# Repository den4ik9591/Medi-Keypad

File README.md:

# MIDI Keypad

A custom MIDI keypad PCB with 7 capacitive touch keys, 3 mechanical buttons, a rotary encoder, 2 slide potentiometers and 3 RGB LEDs, all controlled by an ESP32-S3.

Made for Half Life (Week 3), following the MIDI keypad guide and then changing it to make it my own.

## What it has

- **7 touch keys:** large copper pads on the PCB that work like piano keys. I designed the key footprint myself.
- **3 Kailh Choc buttons:** for extra controls.
- **Rotary encoder (EC11):** for volume or scrolling.
- **2 slide potentiometers (Bourns PTA1543):** for smooth controls like pitch or volume.
- **3 SK6812 MINI-E LEDs:** chained on one data pin.
- **Microcontroller:** Waveshare ESP32-S3-Zero.
- **Board:** 2 layers, about 99.8 x 90.15 mm.

## Pin connections

| Part | ESP32-S3-Zero pin |
| --- | --- |
| Touch key 1 to 7 | GPIO 12, 10, 7, 11, 9, 8, 13 |
| Buttons SW1, SW2, SW3 | GPIO 4, 5, 6 |
| Slider RV2, RV1 | GPIO 1, 2 |
| LED data (DIN) | GPIO 3 |
| Encoder A, B | TX, RX |

Check these against the schematic before building, in case I changed a pin later.

## Files

- `Production/`: files for the PCB manufacturer
- `Images/`: screenshots of the design

## How I made it

1. Followed the guide and drew the schematic in KiCad. I changed the layout a few times so the PCB would be easier to wire.
2. Designed my own touch key footprint and tuned the dimensions.
3. Fixed the key connections in the schematic so every key reaches the ESP32.
4. Placed the parts and routed the board, using the Freerouting plugin for the rest.
5. Ran DRC and fixed the clearance and board edge errors.
6. Exported the production files with the JLCPCB Fabrication Toolkit and got a quote.

## Status

- [x] Schematic
- [x] PCB placed and routed
- [x] DRC fully clean
- [x] Case designed
- [x] Firmware
- [ ] Parts ordered and board built

## What I learned

- How to make a custom footprint for capacitive touch keys, and why touch pads should stay away from other copper.
- How nets work: a pad can only be wired to pads on the same net.
- How to use an autorouter and read a DRC report.

## Credits

Based on the MIDI Keypad guide: https://github.com/KaiPereira/MIDI-Keypad

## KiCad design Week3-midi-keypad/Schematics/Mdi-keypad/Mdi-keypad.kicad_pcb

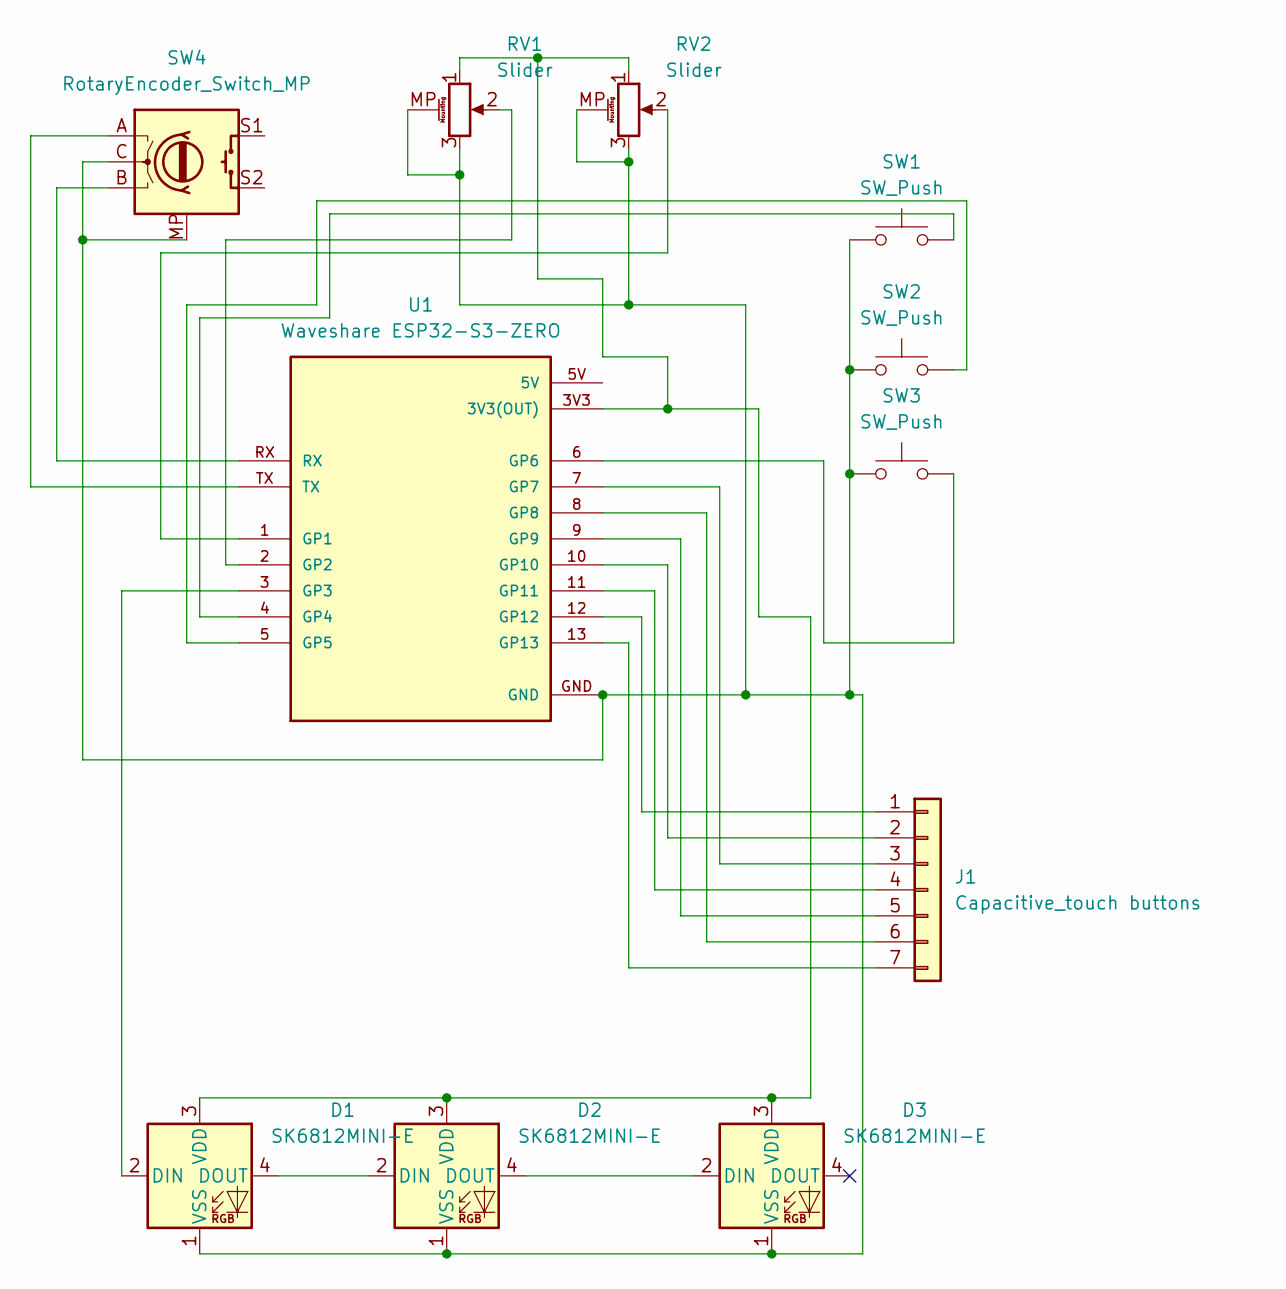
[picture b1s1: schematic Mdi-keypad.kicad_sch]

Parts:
D1, D2, D3: SK6812MINI-E; LED_SK6812MINI-E_3.2x2.8mm_P1.5mm_ReverseMount
J1: Capacitive_touch buttons; Untitled
RV1, RV2: Slider; Potentiometer_Bourns_PTA1543_Single_Slide
SW1, SW2, SW3: SW_Push; Kailh Choc Low-Profile Switches
SW4: RotaryEncoder_Switch_MP; RotaryEncoder_Alps_EC11E_Vertical_H20mm
U1: Waveshare ESP32-S3-ZERO; Waveshare ESP32-S3-Zero; PARTREV NA

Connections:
unnamed: D1.2 (DIN), U1.3 (GP3)
unnamed: D1.4 (DOUT), D2.2 (DIN)
unnamed: D1.3 (VDD), D2.3 (VDD), D3.3 (VDD), RV1.1, RV2.1, U1.3V3 (3V3(OUT))
unnamed: D1.1 (VSS), D2.1 (VSS), D3.1 (VSS), RV1.3, RV1.MP (MountPin), RV2.3, RV2.MP (MountPin), SW1.1, SW2.1, SW3.1, SW4.C, SW4.MP, U1.GND
unnamed: D2.4 (DOUT), D3.2 (DIN)
unnamed: J1.1, U1.12 (GP12)
unnamed: J1.2, U1.10 (GP10)
unnamed: J1.3, U1.7 (GP7)
unnamed: J1.4, U1.11 (GP11)
unnamed: J1.5, U1.9 (GP9)
unnamed: J1.6, U1.8 (GP8)
unnamed: J1.7, U1.13 (GP13)
unnamed: SW4.A, U1.TX
unnamed: SW4.B, U1.RX
unnamed: RV2.2, U1.1 (GP1)
unnamed: RV1.2, U1.2 (GP2)
unnamed: SW1.2, U1.4 (GP4)
unnamed: SW2.2, U1.5 (GP5)
unnamed: SW3.2, U1.6 (GP6)

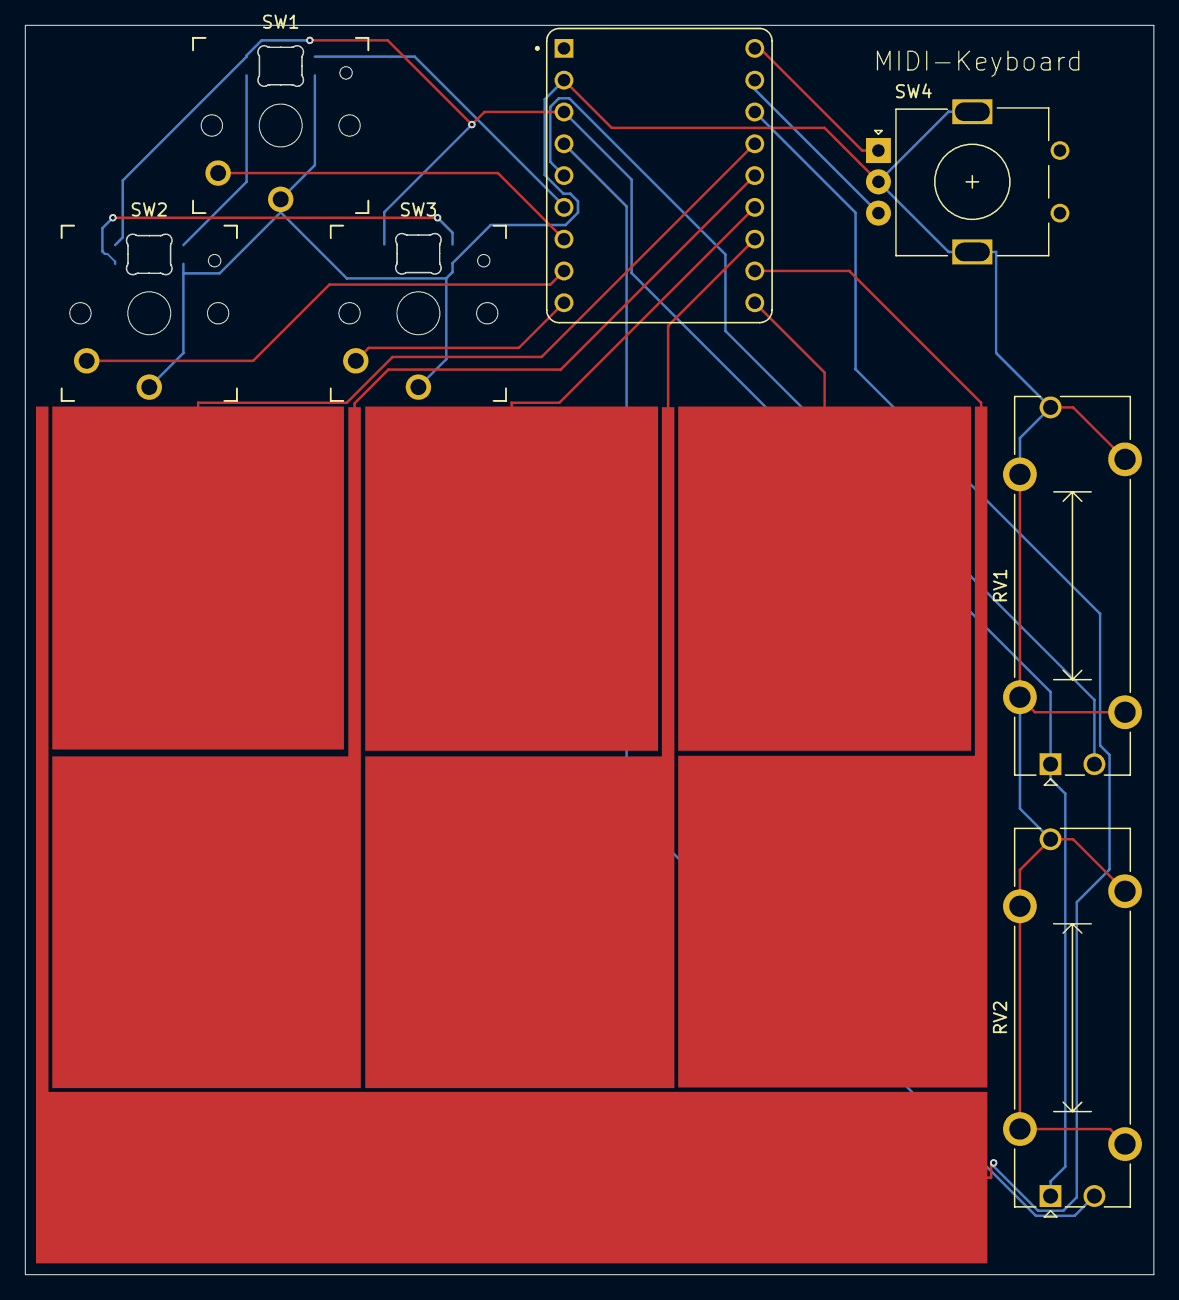
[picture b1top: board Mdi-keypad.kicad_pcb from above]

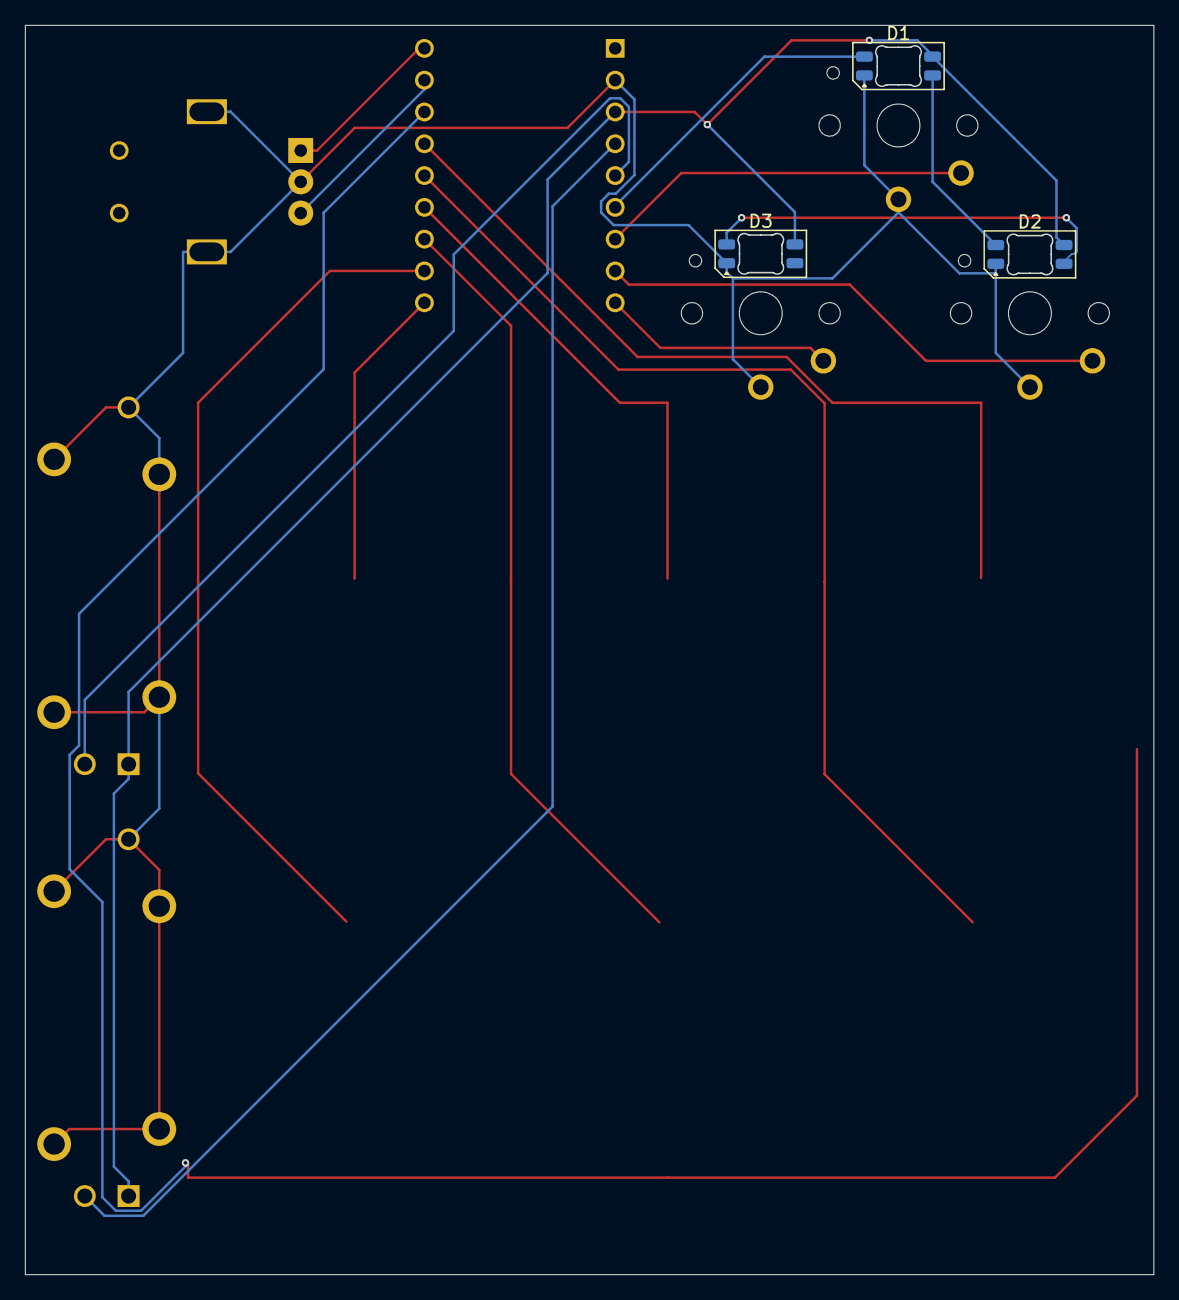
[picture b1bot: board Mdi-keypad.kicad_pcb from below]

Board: 2 copper layers, 90.2 x 99.8 mm, 11 parts (3 on the bottom side), 19 nets.

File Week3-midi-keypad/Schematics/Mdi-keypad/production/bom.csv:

Designator,Footprint,Quantity,Value,LCSC Part #
"D1, D2, D3",LED_SK6812MINI-E_3.2x2.8mm_P1.5mm_ReverseMount,3,SK6812MINI-E,
J1,Untitled,1,Capacitive_touch buttons,
"RV1, RV2",Potentiometer_Bourns_PTA1543_Single_Slide,2,Slider,
"SW1, SW2, SW3",Kailh Choc Low-Profile Switches,3,SW_Push,
SW4,RotaryEncoder_Alps_EC11E_Vertical_H20mm,1,RotaryEncoder_Switch_MP,
U1,Waveshare ESP32-S3-Zero,1,Waveshare ESP32-S3-ZERO,
